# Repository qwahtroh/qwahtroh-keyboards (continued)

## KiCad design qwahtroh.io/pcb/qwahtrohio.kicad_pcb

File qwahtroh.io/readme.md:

# qwahtroh.io

An Upgraded “Plaid” Inspired 12-Key (3x4) Macropad With Fancy Features.

- Keyboard Maintainer: [Garret G.](https://github.com/TheRoyalSweatshirt)
- Hardware Supported: qwahtroh.io, Pro Micro, Elite-C, Proton C, BlueMicro.
- Hardware Availability: Through GitHub

Make example for this keyboard (after setting up your build environment):

    make qwahtroh/qwahtrohio:default

See the [build environment setup](https://docs.qmk.fm/#/getting_started_build_tools) and the [make instructions](https://docs.qmk.fm/#/getting_started_make_guide) for more information. Brand new to QMK? Start with our [Complete Newbs Guide](https://docs.qmk.fm/#/newbs).

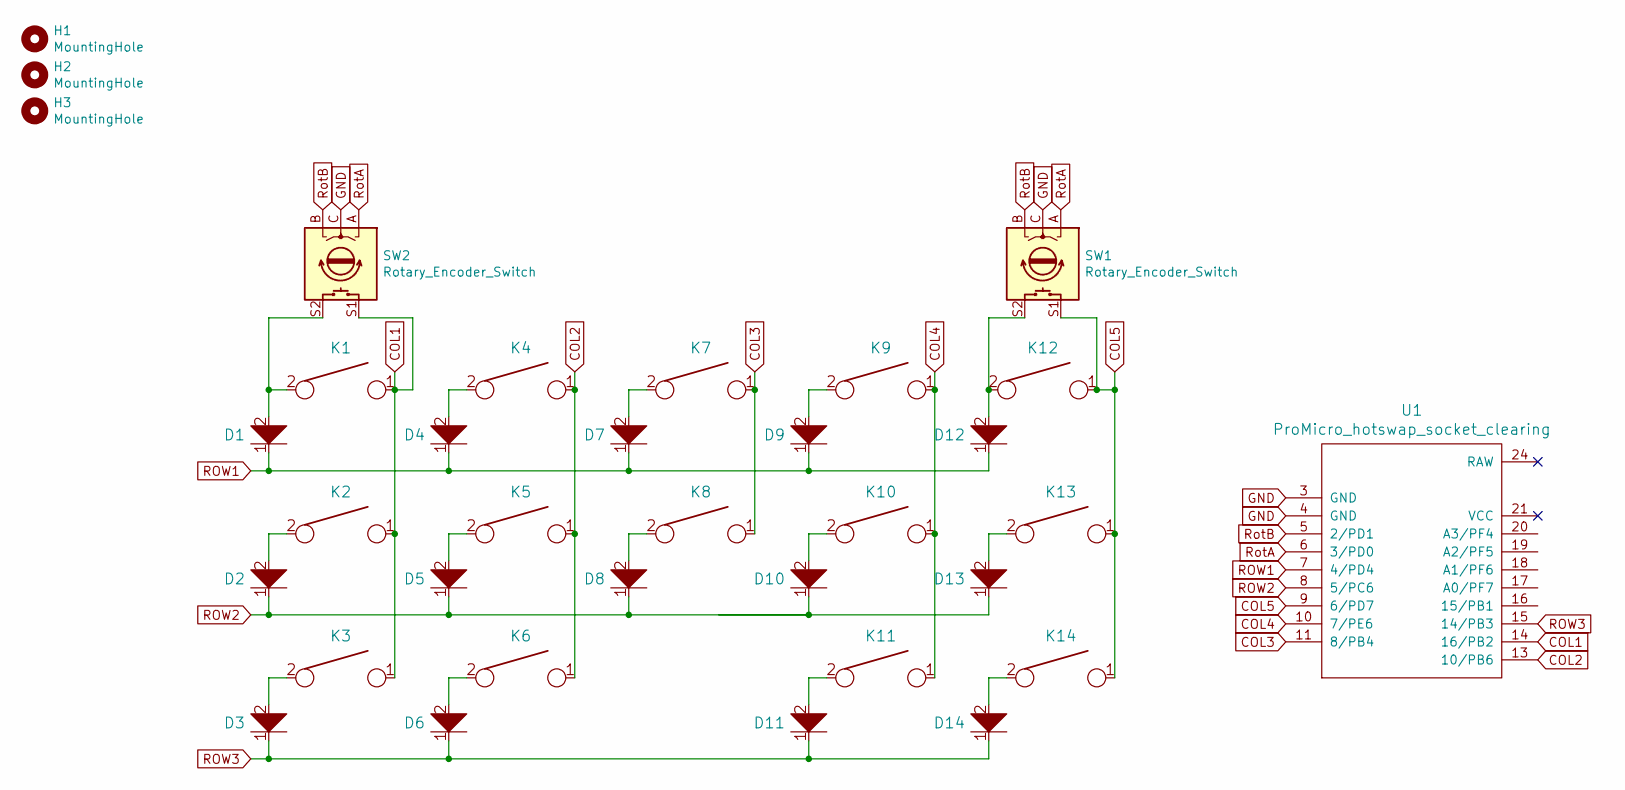
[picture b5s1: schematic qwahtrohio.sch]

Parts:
D1, D2, D3, D4, D5, D6, D7, D8, D9, D10, D11, D12, D13, D14: D; Diode
H1, H2, H3: MountingHole; HOLE_M3
K1, K2, K3, K4, K5, K7, K8, K9, K10, K12, K13, K14: KEYSW; Kailh_MX_Socket
K6, K11: KEYSW; Kailh_MX_Socket_1.25u
SW1, SW2: Rotary_Encoder_Switch; RotaryEncoder_EC11
U1: ProMicro_hotswap_socket_clearing; ArduinoProMicro_hotswap_socket_clear

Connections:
COL1: K1.1, K2.1, K3.1, SW2.S1, U1.14 (16/PB2)
COL2: K4.1, K5.1, K6.1, U1.13 (10/PB6)
COL3: K7.1, K8.1, U1.11 (8/PB4)
COL4: K9.1, K10.1, K11.1, U1.10 (7/PE6)
COL5: K12.1, K13.1, K14.1, SW1.S1, U1.9 (6/PD7)
GND: SW1.C, SW2.C, U1.3 (GND), U1.4 (GND)
unnamed: D1.2, K1.2, SW2.S2
unnamed: D2.2, K2.2
unnamed: D3.2, K3.2
unnamed: D4.2, K4.2
unnamed: D5.2, K5.2
unnamed: D6.2, K6.2
unnamed: D7.2, K7.2
unnamed: D8.2, K8.2
unnamed: D9.2, K9.2
unnamed: D10.2, K10.2
unnamed: D11.2, K11.2
unnamed: D12.2, K12.2, SW1.S2
unnamed: D13.2, K13.2
unnamed: D14.2, K14.2
ROW1: D1.1, D4.1, D7.1, D9.1, D12.1, U1.7 (4/PD4)
ROW2: D2.1, D5.1, D8.1, D10.1, D13.1, U1.8 (5/PC6)
ROW3: D3.1, D6.1, D11.1, D14.1, U1.15 (14/PB3)
RotA: SW1.A, SW2.A, U1.6 (3/PD0)
RotB: SW1.B, SW2.B, U1.5 (2/PD1)

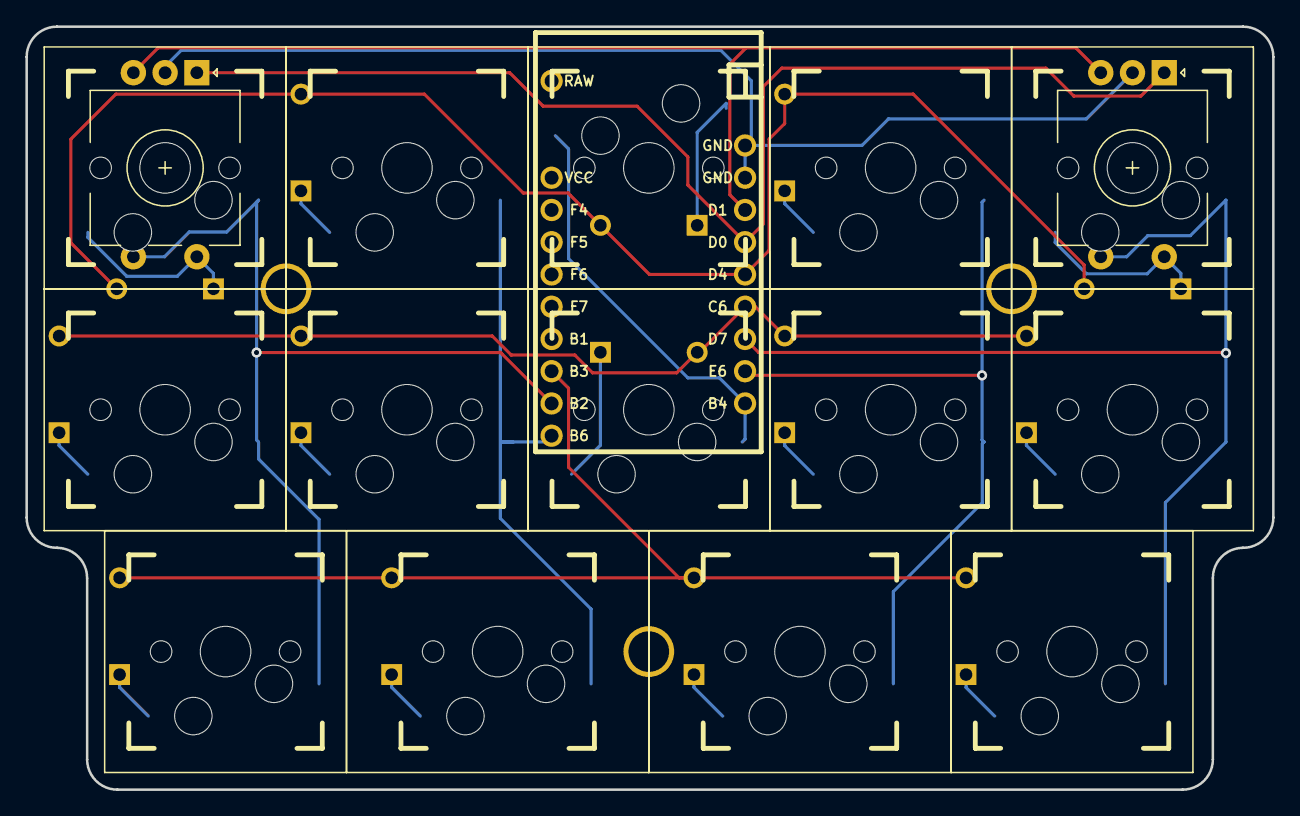
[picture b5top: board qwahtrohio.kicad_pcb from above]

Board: 2 copper layers, 98.2 x 60.1 mm, 34 parts (1 on the bottom side), 25 nets.

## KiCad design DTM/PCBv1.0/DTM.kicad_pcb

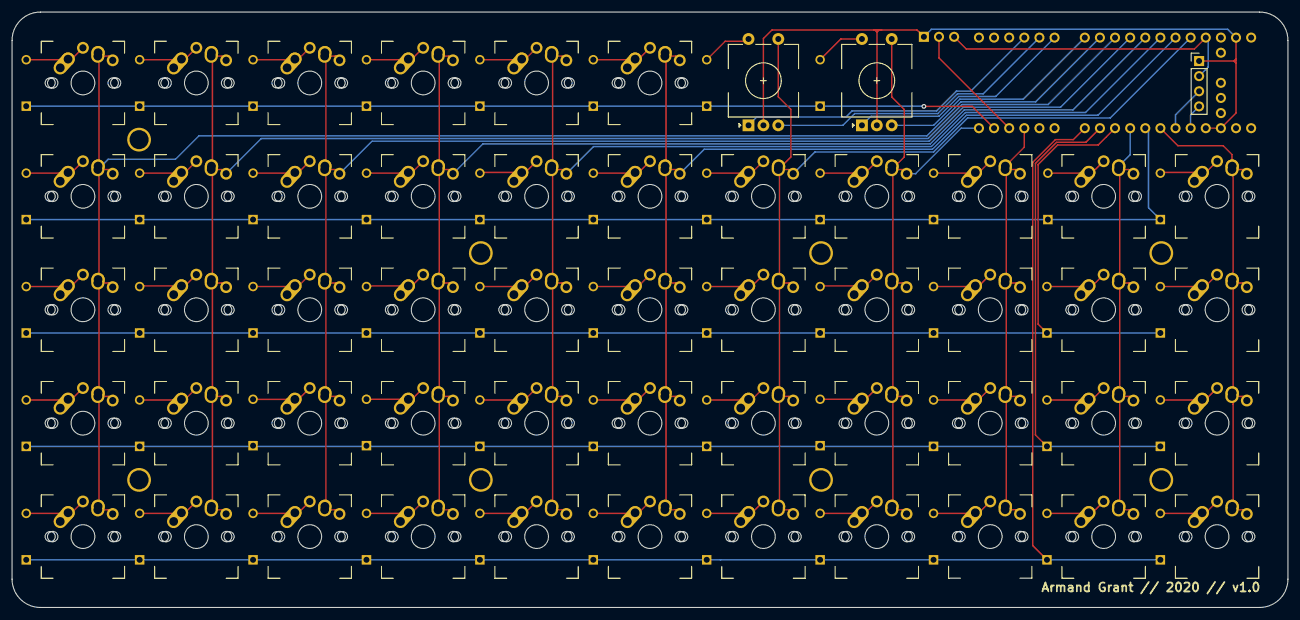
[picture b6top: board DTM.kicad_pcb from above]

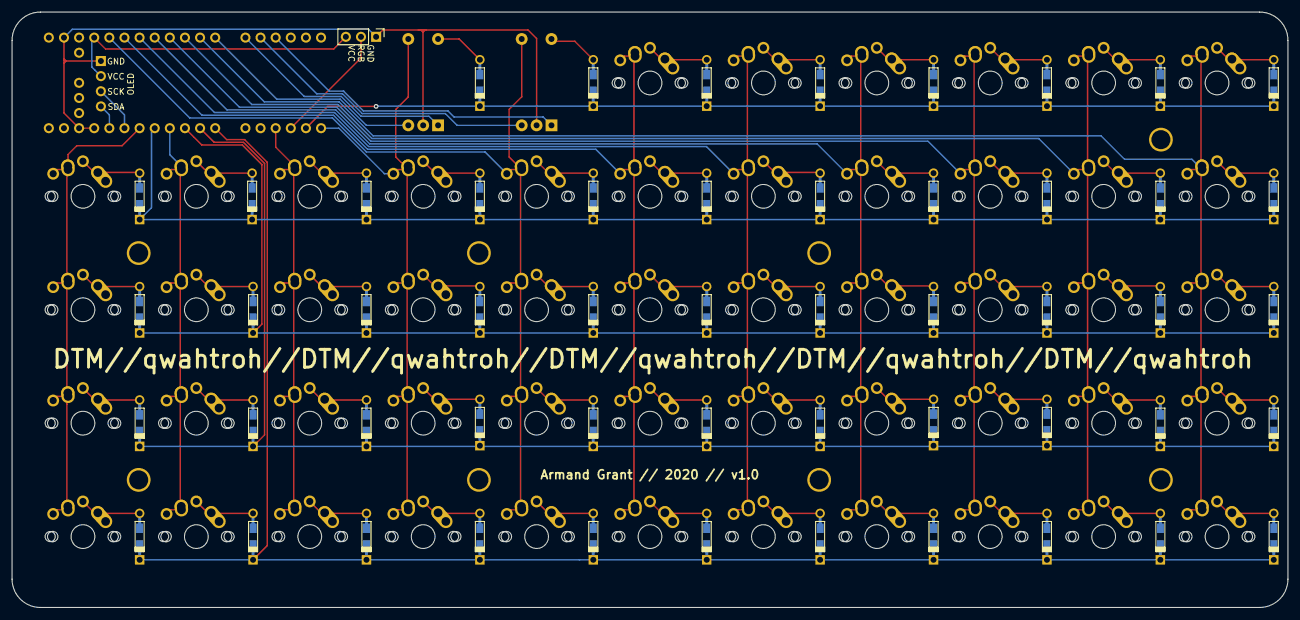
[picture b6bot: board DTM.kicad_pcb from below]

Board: 2 copper layers, 214.3 x 100.0 mm, 115 parts (2 on the bottom side), 74 nets.

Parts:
D1, D2, D3, D4, D5, D6, D7, D8, D9, D10, D11, D12, D13, D14, D15, D16, D17, D18, D19, D20, D21, D22, D23, D24, D25, D26, D27, D28, D29, D30, D31, D32, D33, D34, D35, D36, D37, D38, D39, D40, D41, D42, D43, D44, D45, D46, D47, D48, D49, D50, D51, D52: D; Diode-Hybrid-Back
H1, H2, H3, H4, H5, H6, H7, H8: MountingHole; HOLE_M3
K1, K2, K3, K4, K5, K6, K9, K10, K11, K12, K13, K14, K15, K16, K17, K18, K19, K20, K21, K22, K23, K24, K25, K26, K27, K28, K29, K30, K31, K32, K33, K34, K35, K36, K37, K38, K39, K40, K41, K42, K43, K44, K45, K46, K47, K48, K49, K50, K51, K52: KEYSW; MX-Alps-Choc-1U-NoLED
K7/SW1, K8/SW2: Rotary_Encoder_Switch; RotaryEncoder_EC11
O1: OLED; PinHeader_1x04_P2.54mm_Vertical
RGB1: Conn_01x03; PinHeader_1x03_P2.54mm_Vertical
U1: Proton_C; proton_c

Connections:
COL1: K1.1, K9.1, K20.1, K31.1, K42.1, U1.B15
COL2: K2.1, K10.1, K21.1, K32.1, K43.1, U1.B14
COL3: K3.1, K11.1, K22.1, K33.1, K44.1, U1.B13
COL4: K4.1, K12.1, K23.1, K34.1, K45.1, U1.B8
COL5: K5.1, K13.1, K24.1, K35.1, K46.1, U1.A0
COL6: K6.1, K14.1, K25.1, K36.1, K47.1, U1.A1
COL7: K7/SW1.S1, K15.1, K26.1, K37.1, K48.1, U1.A2
COL8: K8/SW2.S1, K16.1, K27.1, K38.1, K49.1, U1.A15
COL9: K17.1, K28.1, K39.1, K50.1, U1.A6
COL10: K18.1, K29.1, K40.1, K51.1, U1.B3
COL11: K19.1, K30.1, K41.1, K52.1, U1.B5
GND: K7/SW1.C, K8/SW2.C, O1.1, RGB1.1, U1.GND
unnamed: D1.2, K1.2
unnamed: D2.2, K2.2
unnamed: D3.2, K3.2
unnamed: D4.2, K4.2
unnamed: D5.2, K5.2
unnamed: D6.2, K6.2
unnamed: D7.2, K7/SW1.S2
unnamed: D8.2, K8/SW2.S2
unnamed: D9.2, K9.2
unnamed: D10.2, K10.2
unnamed: D11.2, K11.2
unnamed: D12.2, K12.2
unnamed: D13.2, K13.2
unnamed: D14.2, K14.2
unnamed: D15.2, K15.2
unnamed: D16.2, K16.2
unnamed: D17.2, K17.2
unnamed: D18.2, K18.2
unnamed: D19.2, K19.2
unnamed: D20.2, K20.2
unnamed: D21.2, K21.2
unnamed: D22.2, K22.2
unnamed: D23.2, K23.2
unnamed: D24.2, K24.2
unnamed: D25.2, K25.2
unnamed: D26.2, K26.2
unnamed: D27.2, K27.2
unnamed: D28.2, K28.2
unnamed: D29.2, K29.2
unnamed: D30.2, K30.2
unnamed: D31.2, K31.2
unnamed: D32.2, K32.2
unnamed: D33.2, K33.2
unnamed: D34.2, K34.2
unnamed: D35.2, K35.2
unnamed: D36.2, K36.2
unnamed: D37.2, K37.2
unnamed: D38.2, K38.2
unnamed: D39.2, K39.2
unnamed: D40.2, K40.2
unnamed: D41.2, K41.2
unnamed: D42.2, K42.2
unnamed: D43.2, K43.2
unnamed: D44.2, K44.2
unnamed: D45.2, K45.2
unnamed: D46.2, K46.2
unnamed: D47.2, K47.2
unnamed: D48.2, K48.2
unnamed: D49.2, K49.2
unnamed: D50.2, K50.2
unnamed: D51.2, K51.2
unnamed: D52.2, K52.2
R1A: K7/SW1.A, U1.B12
R1B: K7/SW1.B, U1.B11
R2A: K8/SW2.A, U1.B10
R2B: K8/SW2.B, U1.B9
ROW1: D1.1, D2.1, D3.1, D4.1, D5.1, D6.1, D7.1, D8.1, U1.A8
ROW2: D9.1, D10.1, D11.1, D12.1, D13.1, D14.1, D15.1, D16.1, D17.1, D18.1, D19.1, U1.B4
ROW3: D20.1, D21.1, D22.1, D23.1, D24.1, D25.1, D26.1, D27.1, D28.1, D29.1, D30.1, U1.B2
ROW4: D31.1, D32.1, D33.1, D34.1, D35.1, D36.1, D37.1, D38.1, D39.1, D40.1, D41.1, U1.B1
ROW5: D42.1, D43.1, D44.1, D45.1, D46.1, D47.1, D48.1, D49.1, D50.1, D51.1, D52.1, U1.B0
VCC: O1.2, RGB1.3, U1.3.3V

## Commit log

2021-12-09 keyboard files
2021-12-22 added qwahrrow, updated o'shambles
2022-07-16 blockhead two, no ave, and some other boards
